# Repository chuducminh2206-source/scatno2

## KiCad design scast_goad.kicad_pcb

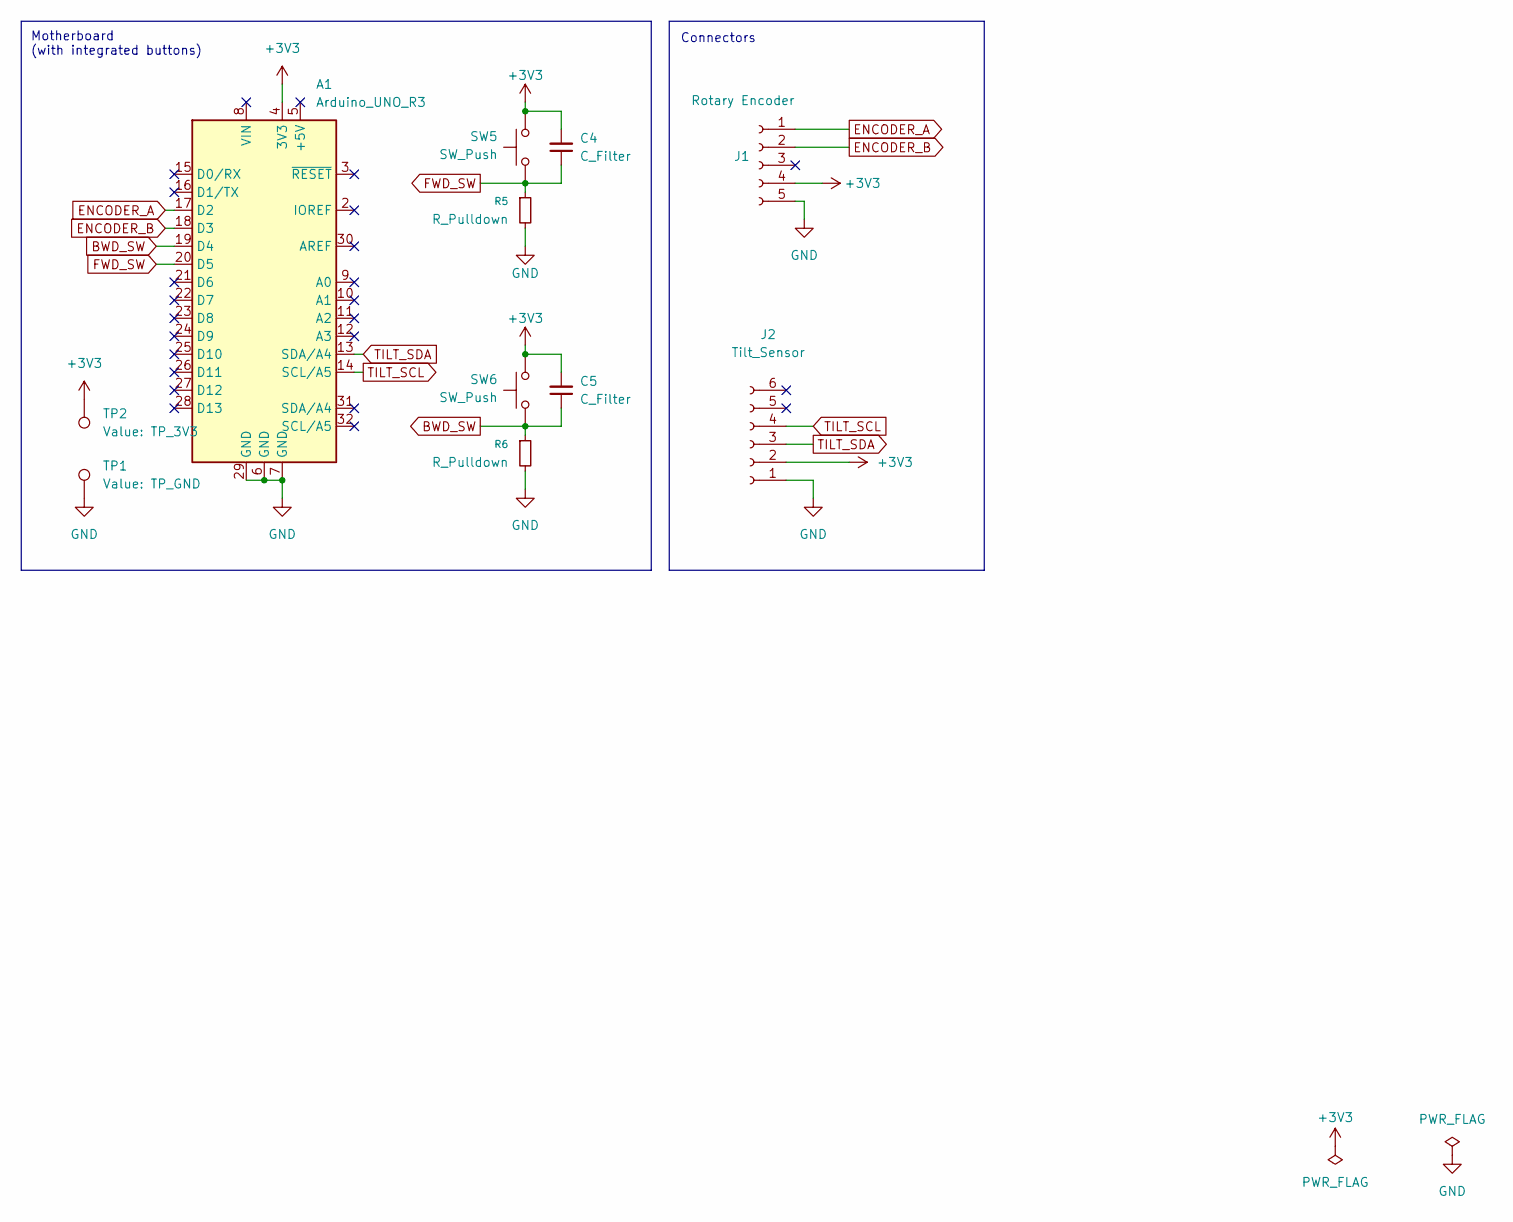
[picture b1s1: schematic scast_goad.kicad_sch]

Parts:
A1: Arduino_UNO_R3
C4, C5: C_Filter; C_Disc_D11.0mm_W5.0mm_P10.00mm
J1: Rotary Encoder; PinSocket_1x05_P2.54mm_Horizontal
J2: Tilt_Sensor; PinSocket_1x06_P2.54mm_Horizontal
R5, R6: R_Pulldown; R_Axial_DIN0414_L11.9mm_D4.5mm_P15.24mm_Horizontal
SW5, SW6: SW_Push; SW_SANWA
TP1: TP_GND; TestPoint_Pad_D4.0mm
TP2: TP_3V3; TestPoint_Pad_4.0x4.0mm

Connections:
+3V3: A1.4 (3V3), C4.2, C5.2, J1.4, J2.2, SW5.2, SW6.2, TP2.1 (1_1)
BWD_SW: A1.19 (D4), C5.1, R6.1, SW6.1
ENCODER_A: A1.17 (D2), J1.1
ENCODER_B: A1.18 (D3), J1.2
FWD_SW: A1.20 (D5), C4.1, R5.1, SW5.1
GND: A1.6 (GND), A1.7 (GND), A1.29 (GND), J1.5, J2.1, R5.2, R6.2, TP1.1 (1_1)
TILT_SCL: A1.14 (SCL/A5), J2.4
TILT_SDA: A1.13 (SDA/A4), J2.3

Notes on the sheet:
Connectors
Motherboard (with integrated buttons)

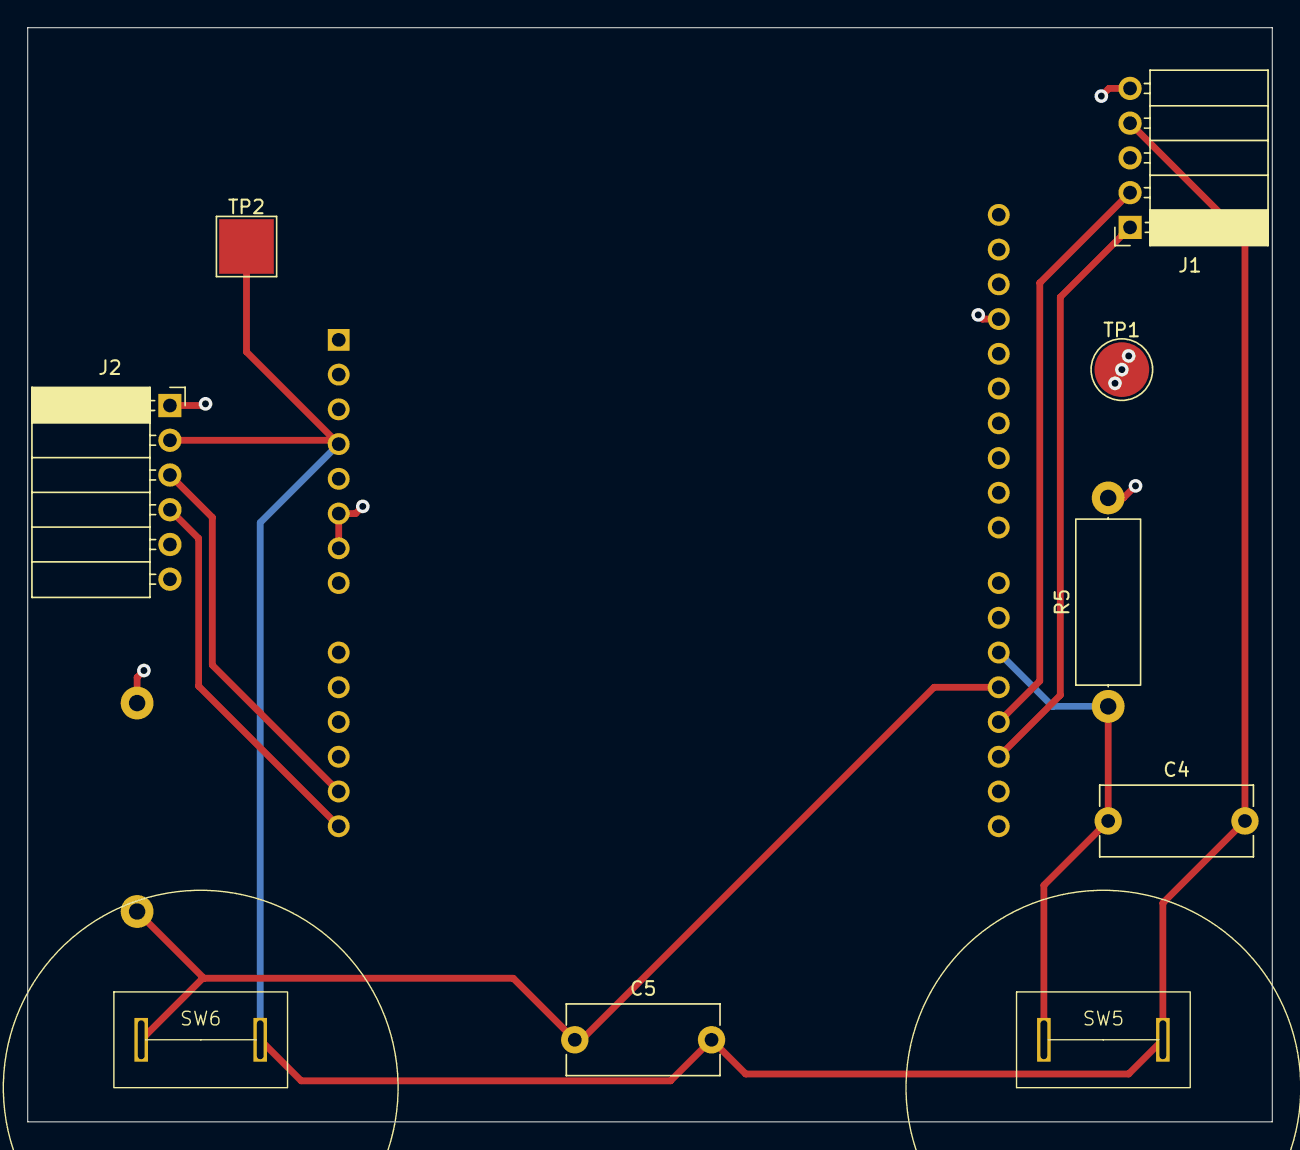
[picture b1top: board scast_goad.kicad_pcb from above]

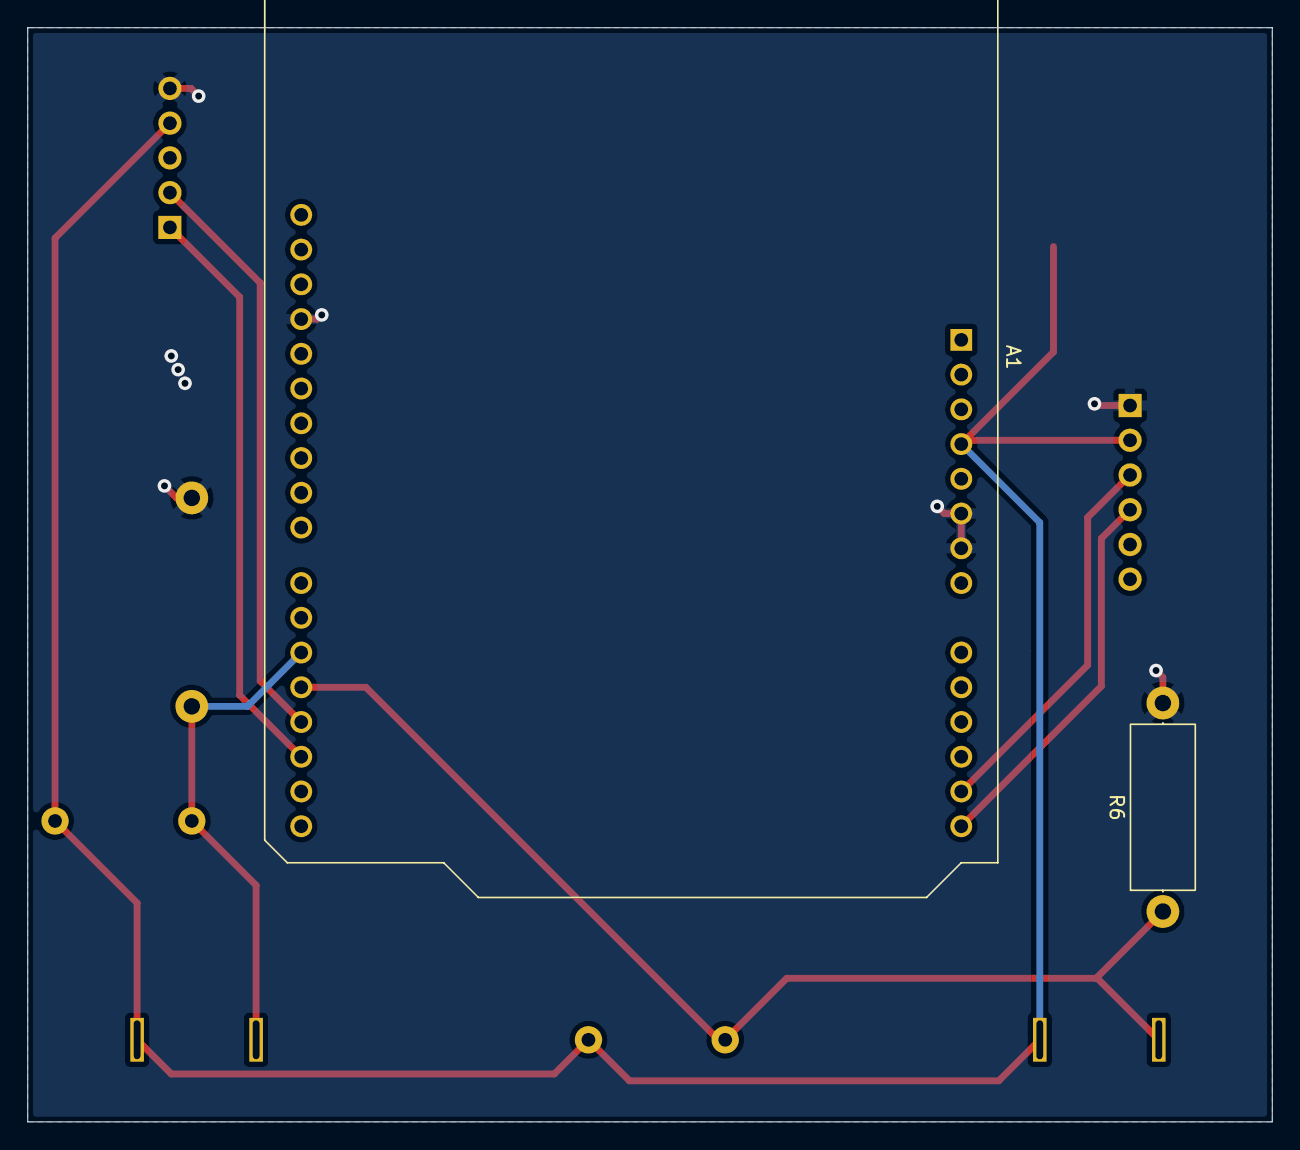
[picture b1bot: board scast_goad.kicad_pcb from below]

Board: 2 copper layers, 91.0 x 80.0 mm, 11 parts (2 on the bottom side), 8 nets.
